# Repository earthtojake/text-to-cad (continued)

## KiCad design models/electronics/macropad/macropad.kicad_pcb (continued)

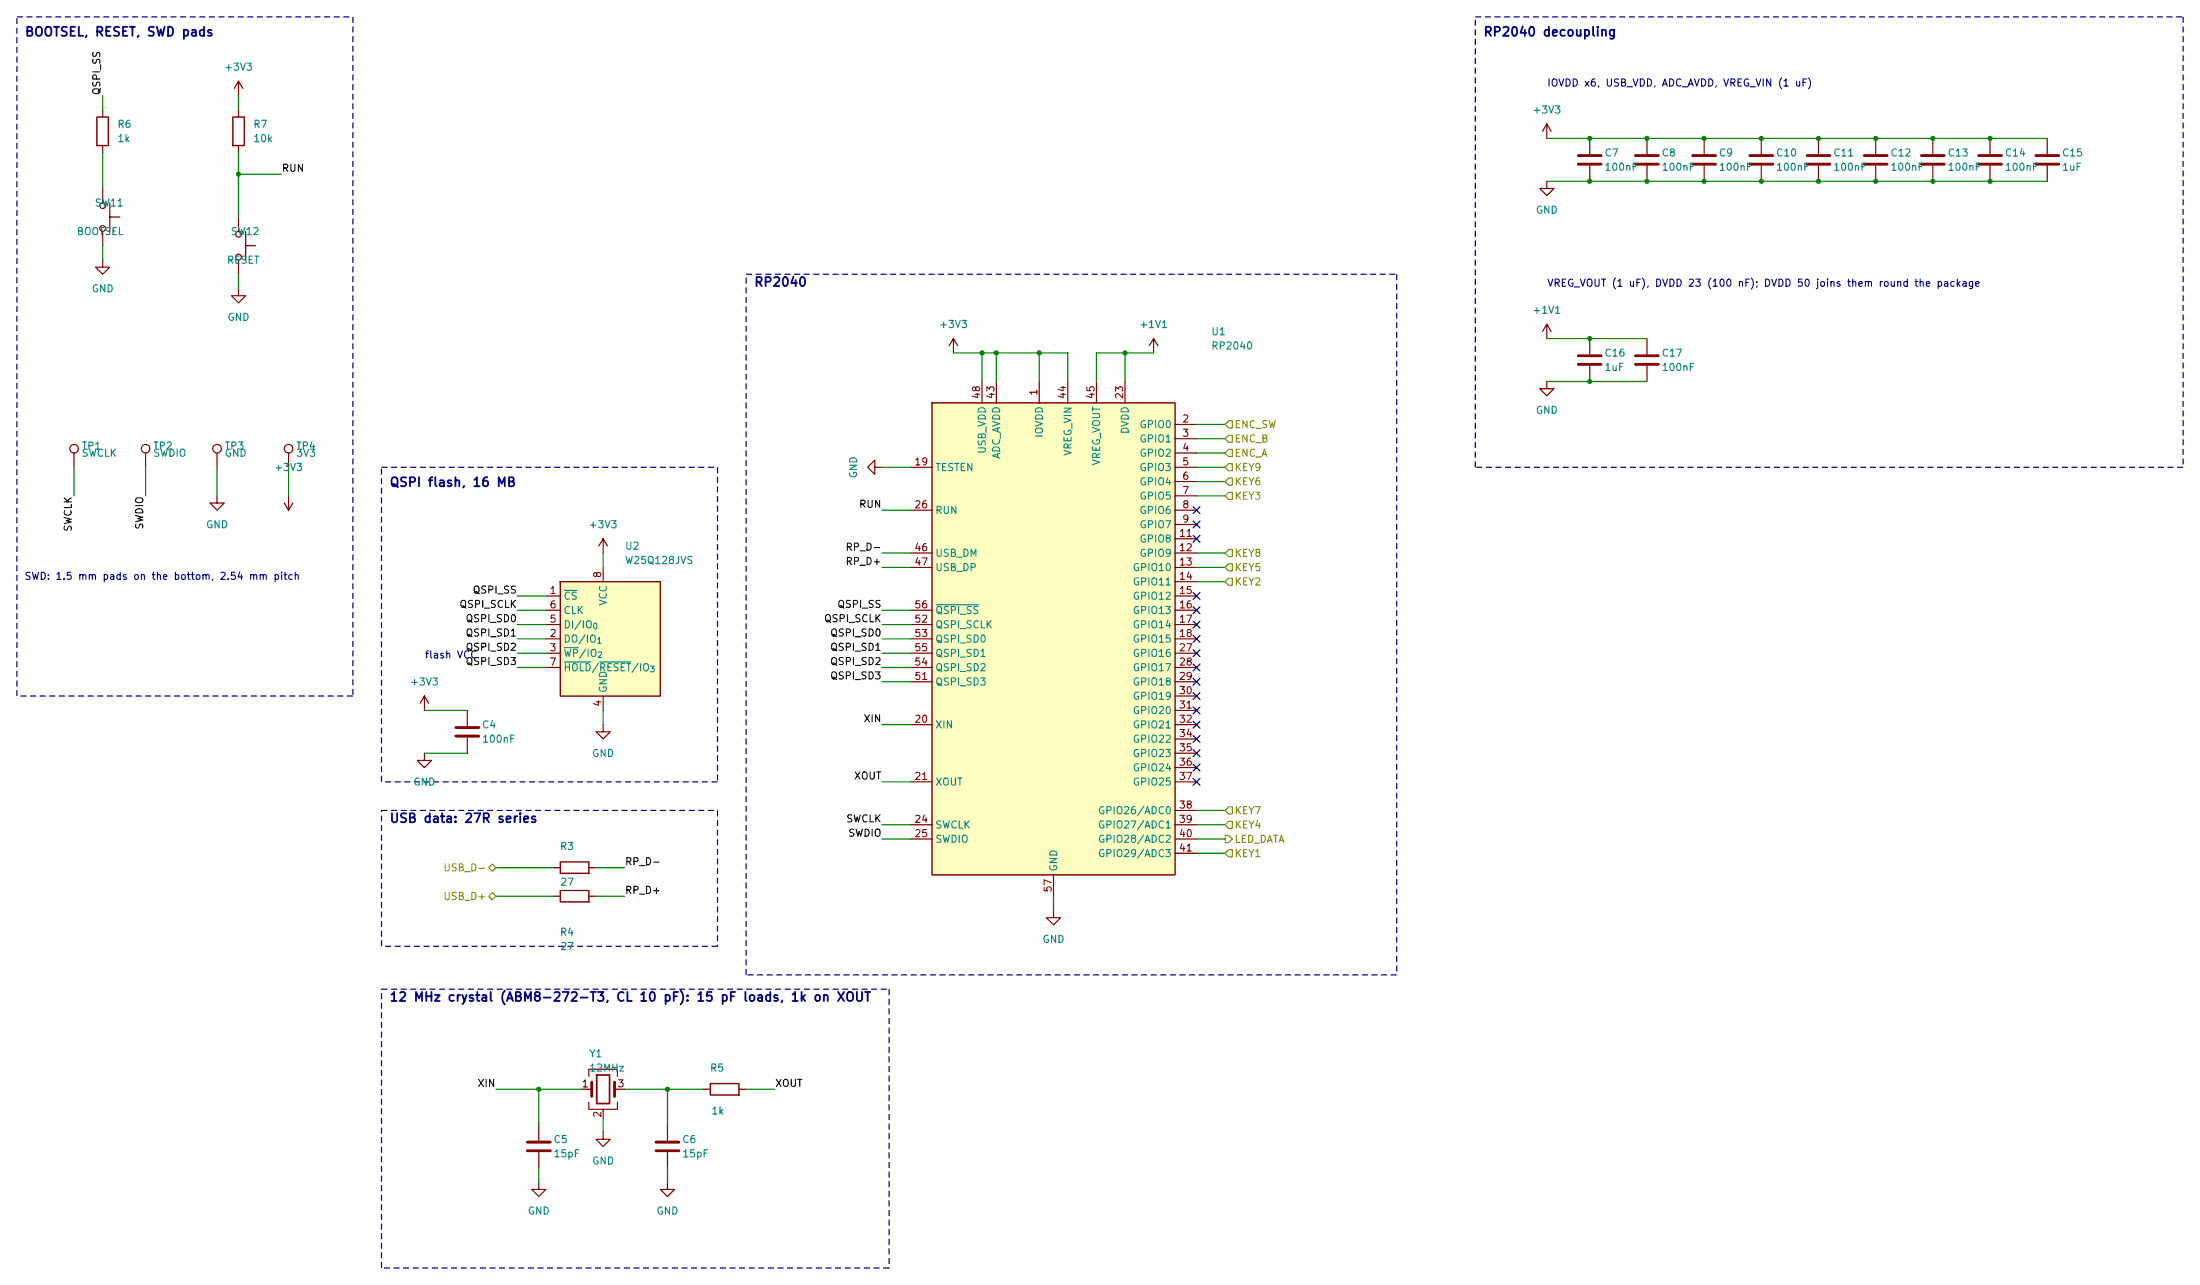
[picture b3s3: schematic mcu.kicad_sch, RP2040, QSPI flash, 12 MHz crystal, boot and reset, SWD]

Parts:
C4, C7, C8, C9, C10, C11, C12, C13, C14, C17: 100nF; C_0402_1005Metric; MPN CL05B104KO5NNNC; LCSC C1525
C5, C6: 15pF; C_0402_1005Metric; MPN CL05C150JB5NNNC; LCSC C1548
C15, C16: 1uF; C_0402_1005Metric; MPN CL05A105KA5NQNC; LCSC C52923
R3, R4: 27; R_0402_1005Metric; MPN 0402WGF270JTCE; LCSC C25100
R5, R6: 1k; R_0402_1005Metric; MPN 0402WGF1001TCE; LCSC C11702
R7: 10k; R_0402_1005Metric; MPN 0402WGF1002TCE; LCSC C25744
SW11: BOOTSEL; SW_SPST_B3U-1000P; MPN B3U-1000P
SW12: RESET; SW_SPST_B3U-1000P; MPN B3U-1000P
TP1: SWCLK; TestPoint_Pad_D1.5mm
TP2: SWDIO; TestPoint_Pad_D1.5mm
TP3: GND; TestPoint_Pad_D1.5mm
TP4: 3V3; TestPoint_Pad_D1.5mm
U1: RP2040; QFN-56-1EP_7x7mm_P0.4mm_EP3.2x3.2mm; MPN RP2040; LCSC C2040
U2: W25Q128JVS; SOIC-8_5.3x5.3mm_P1.27mm; MPN W25Q128JVSIQ; LCSC C97521
Y1: 12MHz; Crystal_SMD_3225-4Pin_3.2x2.5mm; MPN ABM8-272-T3

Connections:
+1V1: C16.1, C17.1, U1.23 (DVDD), U1.45 (VREG_VOUT), U1.50 (DVDD)
+3V3: C4.1, C7.1, C8.1, C9.1, C10.1, C11.1, C12.1, C13.1, C14.1, C15.1, R7.1, TP4.1 (1_1), U1.1 (IOVDD), U1.10 (IOVDD), U1.22 (IOVDD), U1.33 (IOVDD), U1.42 (IOVDD), U1.43 (ADC_AVDD), U1.44 (VREG_VIN), U1.48 (USB_VDD), U1.49 (IOVDD), U2.8 (VCC); also elsewhere on the board
/Keys & LEDs/ENC_A: U1.4 (GPIO2); also elsewhere on the board
/Keys & LEDs/ENC_B: U1.3 (GPIO1); also elsewhere on the board
/Keys & LEDs/ENC_SW: U1.2 (GPIO0); also elsewhere on the board
/Keys & LEDs/KEY1: U1.41 (GPIO29/ADC3); also elsewhere on the board
/Keys & LEDs/KEY2: U1.14 (GPIO11); also elsewhere on the board
/Keys & LEDs/KEY3: U1.7 (GPIO5); also elsewhere on the board
/Keys & LEDs/KEY4: U1.39 (GPIO27/ADC1); also elsewhere on the board
/Keys & LEDs/KEY5: U1.13 (GPIO10); also elsewhere on the board
/Keys & LEDs/KEY6: U1.6 (GPIO4); also elsewhere on the board
/Keys & LEDs/KEY7: U1.38 (GPIO26/ADC0); also elsewhere on the board
/Keys & LEDs/KEY8: U1.12 (GPIO9); also elsewhere on the board
/Keys & LEDs/KEY9: U1.5 (GPIO3); also elsewhere on the board
/Keys & LEDs/LED_DATA: U1.40 (GPIO28/ADC2); also elsewhere on the board
/MCU/QSPI_SCLK: U1.52 (QSPI_SCLK), U2.6 (CLK)
/MCU/QSPI_SD0: U1.53 (QSPI_SD0), U2.5 (DI/IO_{0})
/MCU/QSPI_SD1: U1.55 (QSPI_SD1), U2.2 (DO/IO_{1})
/MCU/QSPI_SD2: U1.54 (QSPI_SD2), U2.3 (~WP/IO_{2})
/MCU/QSPI_SD3: U1.51 (QSPI_SD3), U2.7 (~HOLD/~RESET/IO_{3})
/MCU/QSPI_SS: R6.1, U1.56 (~QSPI_SS), U2.1 (~CS)
/MCU/RP_D+: R4.2, U1.47 (USB_DP)
/MCU/RP_D-: R3.2, U1.46 (USB_DM)
/MCU/RUN: R7.2, SW12.1, U1.26 (RUN)
/MCU/SWCLK: TP1.1 (1_1), U1.24 (SWCLK)
/MCU/SWDIO: TP2.1 (1_1), U1.25 (SWDIO)
/MCU/XIN: C5.1, U1.20 (XIN), Y1.1
/MCU/XOUT: R5.2, U1.21 (XOUT)
/USB & Power/USB_D+: R4.1; also elsewhere on the board
/USB & Power/USB_D-: R3.1; also elsewhere on the board
GND: C4.2, C5.2, C6.2, C7.2, C8.2, C9.2, C10.2, C11.2, C12.2, C13.2, C14.2, C15.2, C16.2, C17.2, SW11.2, SW12.2, TP3.1 (1_1), U1.19 (TESTEN), U1.57 (GND), U2.4 (GND), Y1.2 (G), Y1.4 (G); also elsewhere on the board
unnamed: C6.1, R5.1, Y1.3
unnamed: R6.2, SW11.1

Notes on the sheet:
RP2040
QSPI flash, 16 MB
flash VCC
USB data: 27R series
12 MHz crystal (ABM8-272-T3, CL 10 pF): 15 pF loads, 1k on XOUT
BOOTSEL, RESET, SWD pads
SWD: 1.5 mm pads on the bottom, 2.54 mm pitch
RP2040 decoupling
IOVDD x6, USB_VDD, ADC_AVDD, VREG_VIN (1 uF)
VREG_VOUT (1 uF), DVDD 23 (100 nF); DVDD 50 joins them round the package

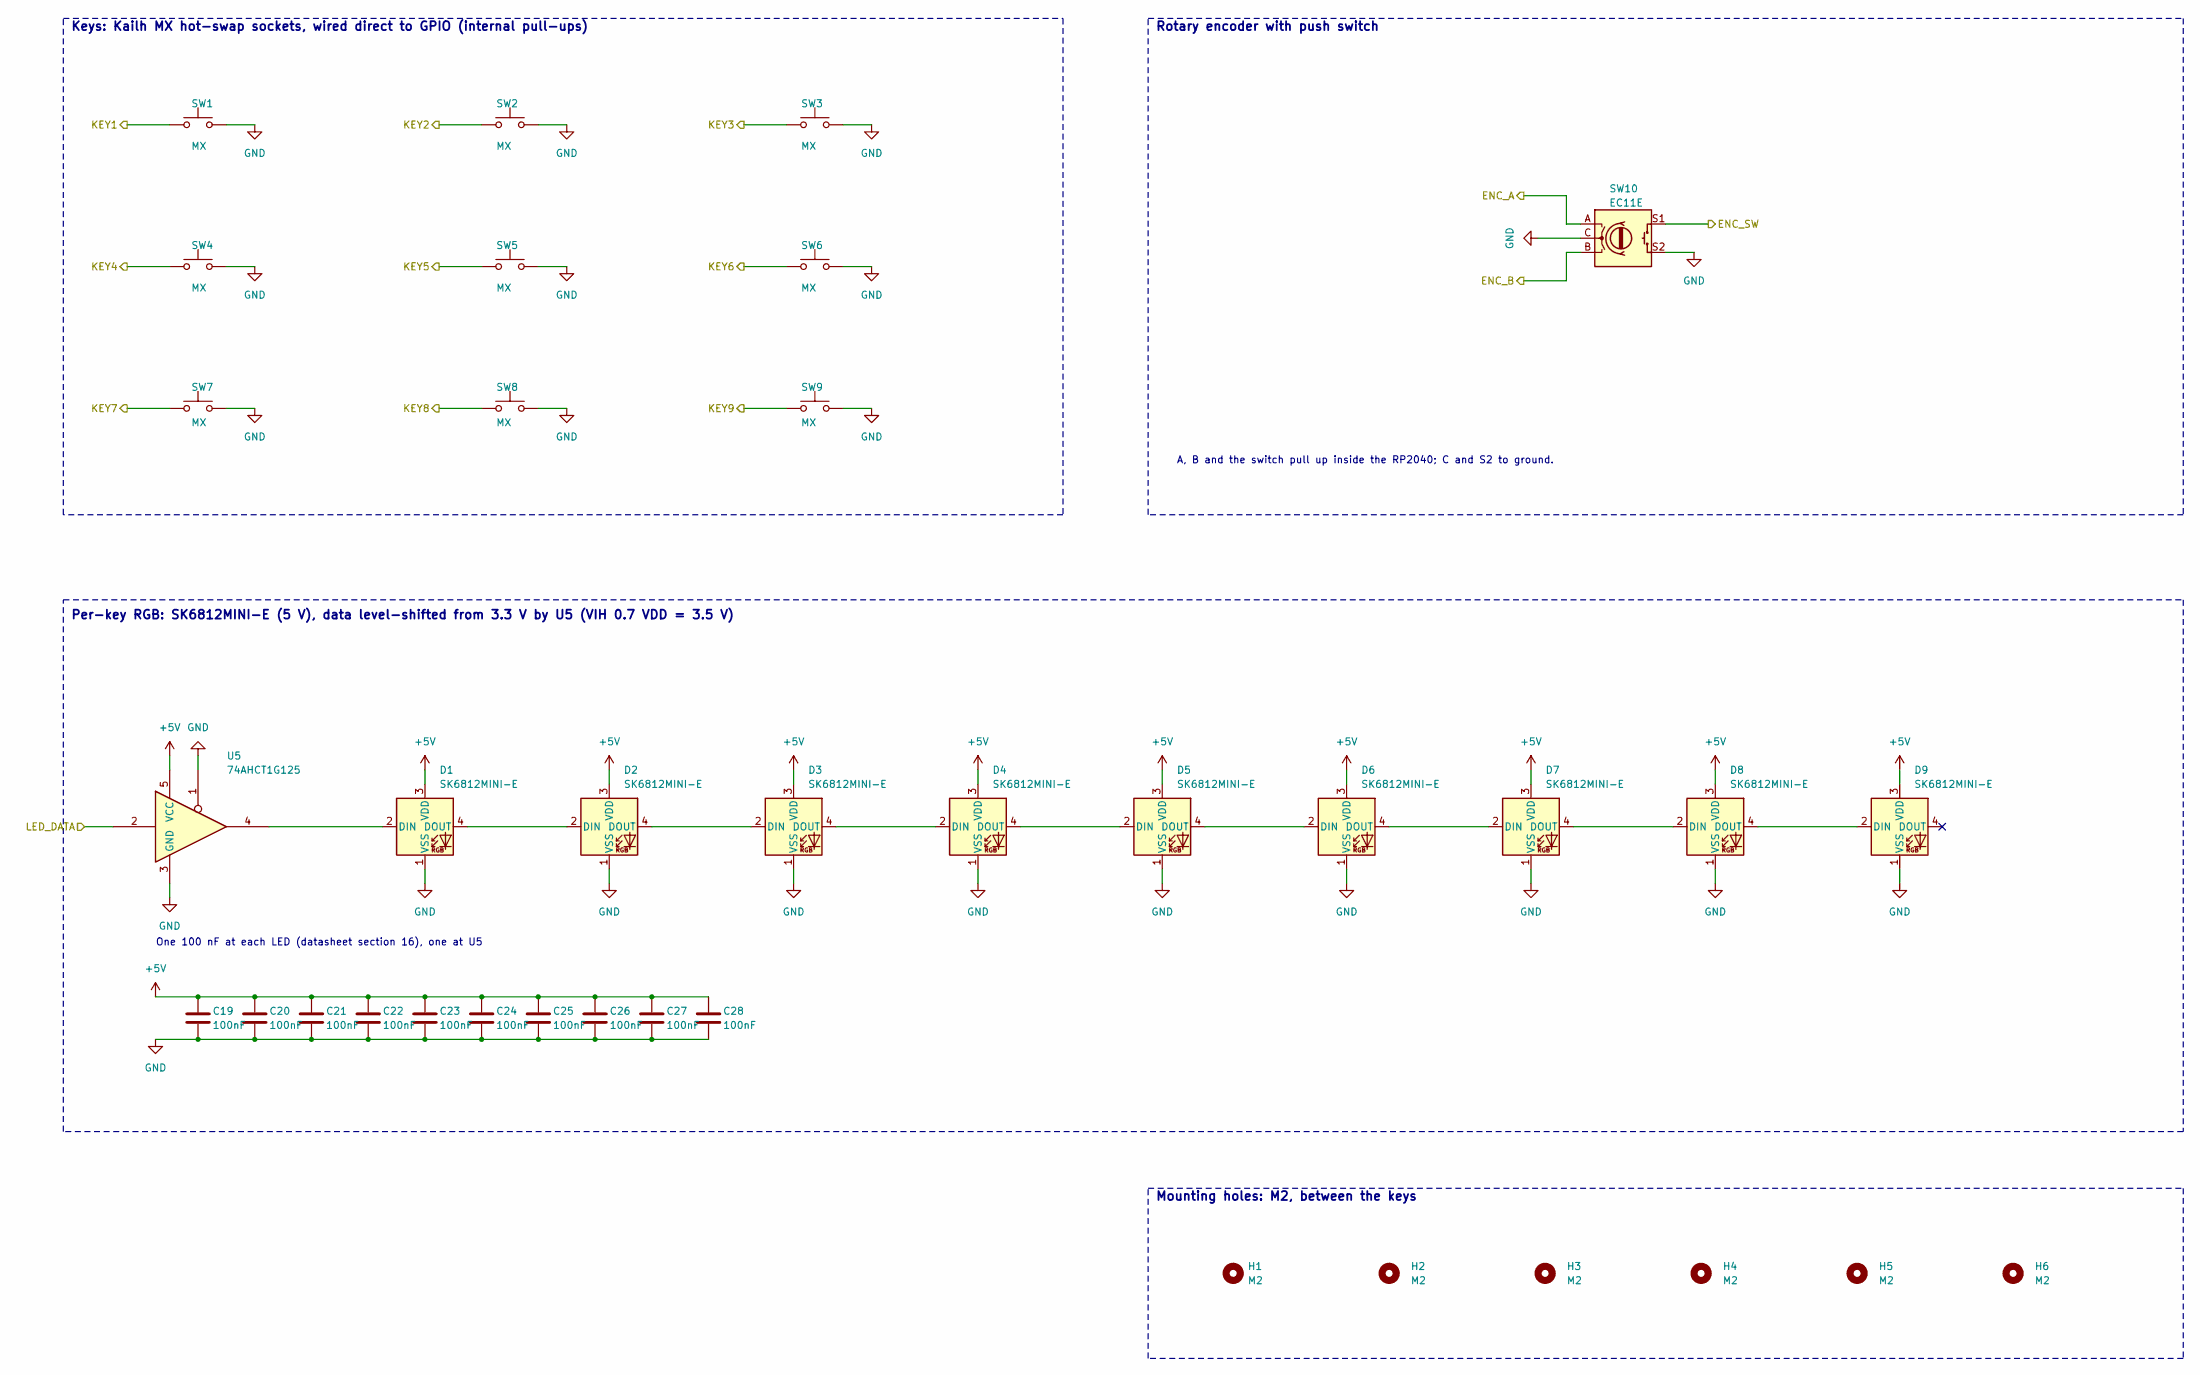
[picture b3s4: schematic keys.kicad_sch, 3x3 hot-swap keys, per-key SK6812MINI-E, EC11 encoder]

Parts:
C19, C20, C21, C22, C23, C24, C25, C26, C27, C28: 100nF; C_0402_1005Metric; MPN CL05B104KO5NNNC; LCSC C1525
D1, D2, D3, D4, D5, D6, D7, D8, D9: SK6812MINI-E; LED_SK6812MINI-E_3.2x2.8mm_P1.5mm_ReverseMount; MPN SK6812MINI-E; LCSC C5149201
H1, H2, H3, H4, H5, H6: M2; MountingHole_2.2mm_M2
SW1, SW2, SW3, SW4, SW5, SW6, SW7, SW8, SW9: MX; SW_Kailh_HotSwap_MX_1.00u; MPN CPG151101S11
SW10: EC11E; RotaryEncoder_Alps_EC11E-Switch_Vertical_H20mm; MPN EC11E18244A5
U5: 74AHCT1G125; SOT-23-5; MPN 74AHCT1G125GV,125

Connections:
+5V: C19.1, C20.1, C21.1, C22.1, C23.1, C24.1, C25.1, C26.1, C27.1, C28.1, D1.3 (VDD), D2.3 (VDD), D3.3 (VDD), D4.3 (VDD), D5.3 (VDD), D6.3 (VDD), D7.3 (VDD), D8.3 (VDD), D9.3 (VDD), U5.5 (VCC); also elsewhere on the board
/Keys & LEDs/ENC_A: SW10.A; also elsewhere on the board
/Keys & LEDs/ENC_B: SW10.B; also elsewhere on the board
/Keys & LEDs/ENC_SW: SW10.S1; also elsewhere on the board
/Keys & LEDs/KEY1: SW1.1; also elsewhere on the board
/Keys & LEDs/KEY2: SW2.1; also elsewhere on the board
/Keys & LEDs/KEY3: SW3.1; also elsewhere on the board
/Keys & LEDs/KEY4: SW4.1; also elsewhere on the board
/Keys & LEDs/KEY5: SW5.1; also elsewhere on the board
/Keys & LEDs/KEY6: SW6.1; also elsewhere on the board
/Keys & LEDs/KEY7: SW7.1; also elsewhere on the board
/Keys & LEDs/KEY8: SW8.1; also elsewhere on the board
/Keys & LEDs/KEY9: SW9.1; also elsewhere on the board
/Keys & LEDs/LED_DATA: U5.2; also elsewhere on the board
GND: C19.2, C20.2, C21.2, C22.2, C23.2, C24.2, C25.2, C26.2, C27.2, C28.2, D1.1 (VSS), D2.1 (VSS), D3.1 (VSS), D4.1 (VSS), D5.1 (VSS), D6.1 (VSS), D7.1 (VSS), D8.1 (VSS), D9.1 (VSS), SW1.2, SW2.2, SW3.2, SW4.2, SW5.2, SW6.2, SW7.2, SW8.2, SW9.2, SW10.C, SW10.S2, U5.1, U5.3 (GND); also elsewhere on the board
unnamed: D1.2 (DIN), U5.4
unnamed: D1.4 (DOUT), D2.2 (DIN)
unnamed: D2.4 (DOUT), D3.2 (DIN)
unnamed: D3.4 (DOUT), D4.2 (DIN)
unnamed: D4.4 (DOUT), D5.2 (DIN)
unnamed: D5.4 (DOUT), D6.2 (DIN)
unnamed: D6.4 (DOUT), D7.2 (DIN)
unnamed: D7.4 (DOUT), D8.2 (DIN)
unnamed: D8.4 (DOUT), D9.2 (DIN)

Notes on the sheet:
Keys: Kailh MX hot-swap sockets, wired direct to GPIO (internal pull-ups)
Rotary encoder with push switch
A, B and the switch pull up inside the RP2040; C and S2 to ground.
Per-key RGB: SK6812MINI-E (5 V), data level-shifted from 3.3 V by U5 (VIH 0.7 VDD = 3.5 V)
One 100 nF at each LED (datasheet section 16), one at U5
Mounting holes: M2, between the keys

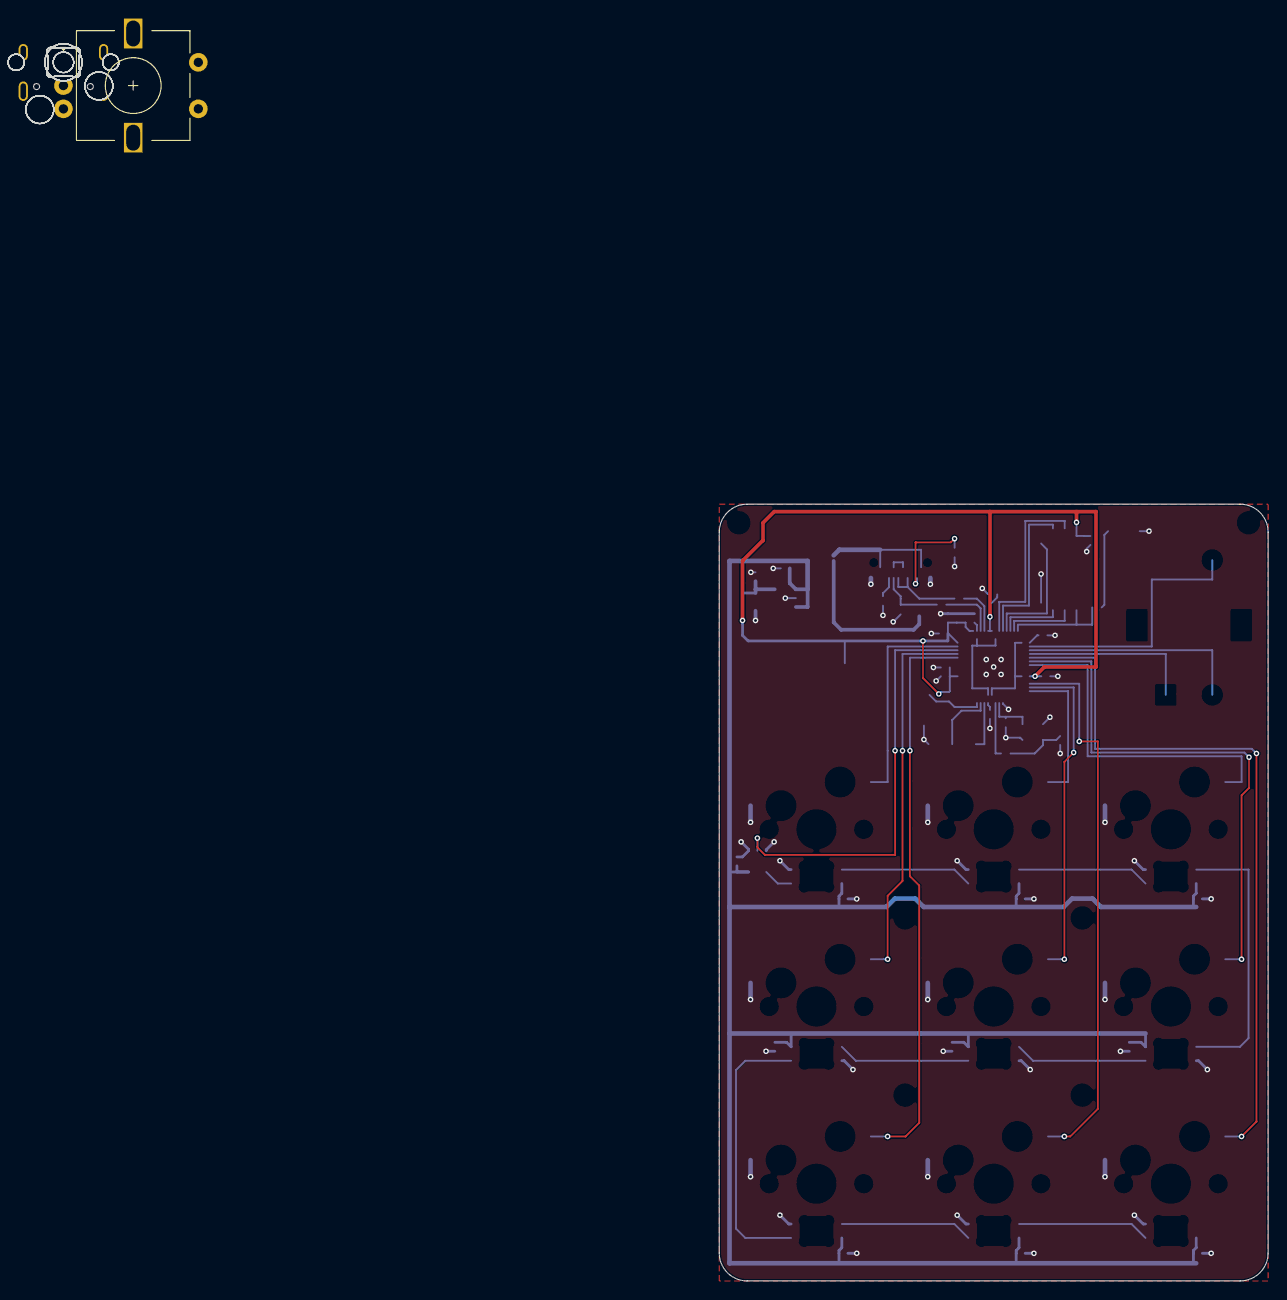
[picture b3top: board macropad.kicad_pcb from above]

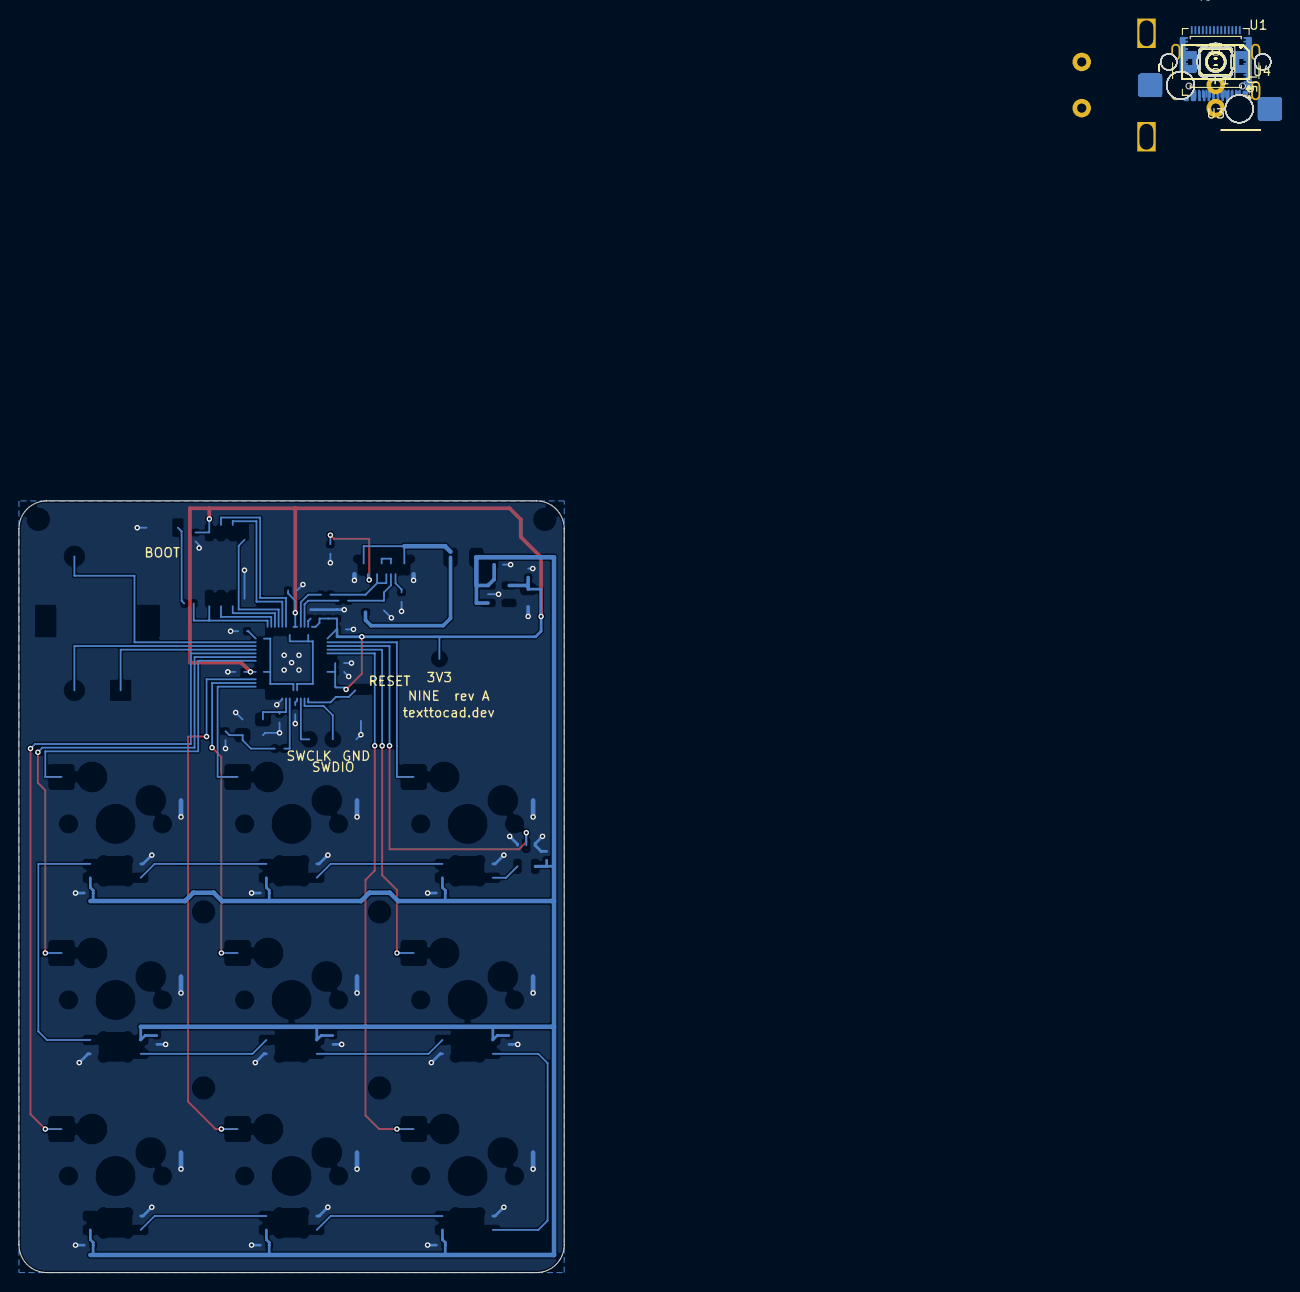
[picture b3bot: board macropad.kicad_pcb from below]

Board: 2 copper layers, 3.6 x 3.2 mm, 73 parts (66 on the bottom side), 46 nets.

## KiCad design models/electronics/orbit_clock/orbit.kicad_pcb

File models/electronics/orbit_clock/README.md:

# Orbit: a round LED ring clock

**Build the board first.** Its KiCad files (the board, the five schematic sheets, the project file, the project
libraries and their tables) are generated by `scripts/`, not committed: `cad run build.py`, from this folder, makes
them in about 30 s. It needs the `cad` command (KiCad 10.99's kicad-cli and API come with it) and KiCad's stock
libraries (macOS's KiCad.app, or `KICAD_STOCK`). Opening the board or the schematic in the viewer or in KiCad,
the checks and the printed parts (`src/`) all read what it writes, so run it before any of them.

A 120 mm round clock face with an outer ring of 60 addressable RGB LEDs (minutes and seconds) and an inner
ring of 12 (hours), an ESP32-C3 on Wi-Fi time, USB-C power and data, auto-dimming from an ambient light
sensor. Three printed parts go round it: a black baffle with a cell for every LED, a thin translucent diffuser,
and a desk stand that holds the clock tilted back 12 degrees with its USB cable hidden underneath.

**Why it is interesting.** The 72 LEDs and 72 capacitors are placed by a few lines of code from a radius and a
count; the LED data chain runs round both rings as copper arcs, one per link; and the baffle's 72 cells line
up with the LEDs because the CAD model reads every LED's position from the saved board file, not from the
script that placed it.

| | |
| --- | --- |
| Board | 120 mm circle with a flat for the USB-C receptacle, 4 layers, 1.6 mm, JLCPCB standard 4-layer rules |
| Parts | 182 footprints: 72 x WS2812B-2020, 72 x 100 nF, ESP32-C3-WROOM-02, USB-C, 26 others |
| Nets | 91; 536 tracks (1.77 m of copper), 71 arcs (the LED chain's links among them), 256 vias |
| Checks | ERC clean (0 warnings); DRC 0 errors, 0 unconnected; 30 warnings: 29 `lib_footprint_mismatch` (footprints placed, turned and flipped over KiCad's API no longer compare equal to their library's) and the module's own silkscreen outline running past the board edge at the antenna |
| Printed | baffle (black PLA), diffuser (natural PETG, 1.2 mm), stand (black PLA); 3MF of each and a two-material front |

## The design

**Front (F.Cu): the face.** The 60 minute LEDs sit on a 50 mm radius, D1 at 12 o'clock, clockwise; the 12 hour
LEDs on a 38 mm radius. Each LED is turned so its local +y points out of the ring: its DOUT (inner row) faces
the next LED and its DIN (outer row) the previous one, so each link is a single arc from one DOUT to the next DIN.
Each LED's 100 nF sits 2.45 mm inside it, with a +5V via and a GND via under its two pads and a GND via outside
the ring at the LED's VSS pad. The ambient light sensor (LTR-303ALS-01, I2C) is at the centre, behind a window
in the baffle. Between the rings at 12 o'clock: the hop from the minute ring's end to the hour ring's start, and
the data input as an arc on a 43.5 mm radius.

**Back (B.Cu): the electronics.** The ESP32-C3-WROOM-02 at the top edge with its antenna at the board's edge and
its own keep-out (no copper on any layer, 5 mm round the antenna, Espressif's rule); the USB-C receptacle on the flat at
the bottom; its USBLC6-2SC6 ESD array in line (flow-through), 5.1k CC pull-downs, a 3 A polyfuse, a 470 uF bulk
capacitor and 22 uF; an AP2112K 3.3 V regulator; a 74AHCT1G125 shifting the LED data from 3.3 V to 5 V with 33 ohm
at the driver; BOOT and RESET; test points for 5V, 3V3, GND, TX and RX (and TP6 at the chain's end on the front).
The CC1/CC2 voltages go to the ESP32's ADC so firmware can cap the LED brightness to what the source advertises.

**Power.** Worst case: 72 LEDs x 3 colours x 12 mA = 2.59 A, plus the ESP32-C3's RF peak (~0.35 A): ~3.0 A, the
most a USB-C source gives at 5 V. The LEDs draw from In2.Cu (a whole-board +5V plane) and return through In1.Cu
(a whole-board GND plane), each by its own vias, so no track carries the ring's current. VBUS runs from both
receptacle pad pairs (0.6 mm stubs, 1.65 A each, IPC-2221 outer 1 oz 10 C), 1.0 mm into the 1210L300 polyfuse
(3 A hold, 6 A trip), out into In2 by two vias. **Why 4 layers:** the 72 LEDs need +5V and GND everywhere round
two rings, the back carries the routing, and the antenna and USB need an unbroken ground: two planes do all three.

**Rules (JLCPCB standard 4-layer, from the pcb skill's manufacturing reference, read 2026-11-04):** 0.15 mm
clearance and minimum track (JLCPCB 0.09/0.09), 0.2 mm signal, 0.6/0.3 mm vias, 0.2 mm minimum drill (the
module's own thermal vias), 0.3 mm copper to edge, 0.19 mm hole clearance (GCT's USB4105 land pattern),
silkscreen 1.0/0.15 mm. Netclasses Default, Power (+5V, VBUS 0.8 mm) and USB in `orbit.kicad_pro`, which `scripts/board.py setup` writes.

**The libraries.** The project carries its own symbols and footprints (`orbit.kicad_sym`, `power.kicad_sym`,
`orbit.pretty`), copied from KiCad's stock ones by `scripts/build_libraries.py`, so ERC and DRC need no library of
the person's. Each footprint names the stock 3D model KiCad's library holds for it (`${KICAD10_3DMODEL_DIR}/...`),
which the board's 3D view and its exports find, but for the two KiCad names and does not ship: the WS2812B-2020
and the LTR-303ALS-01, whose models `src/part_models.py` draws into `orbit.3dshapes/` (`${KIPRJMOD}`).

**The printed parts** (`src/orbit.py`) read the board: the outline (its arc's circle and its flat), the four M3
holes and all 72 LEDs from `orbit.kicad_pcb`, every part's 3D extent from the board's STEP.
- **Baffle**, 8 mm: 60 wedge cells (1.6 mm walls of constant thickness) and 12 round light pipes (7.6 mm), a
  window over the light sensor, pockets underneath for every part outside a cell, M3 pilot holes on the board's
  holes (M3 x 8 self-tapping screws from the back), four peg holes for the diffuser. Prints as modelled, board side
  down.
- **Diffuser**, 1.2 mm natural PETG with a 0.5 mm chamfer and four 3 mm pegs. Prints face down
  (`diffuser_print`). Or print both as one: `front_print` is the diffuser and the baffle stacked as one
  two-material job (face on the plate).
- **Stand**: a 112 x 66 x 34 mm plinth with a saddle that holds the stack by its rim (slot 0.3 mm clear, a lip
  that covers only the outer 4.4 mm of the face, a 6 mm back wall with pockets for the receptacle and the
  polyfuse), tilted back 12 degrees; a pocket for the USB-C plug straight down from the receptacle and a
  45-degree-roofed cable channel under the plinth to the back.

## Files

| Path | What |
| --- | --- |
| `build.py` | the one command that makes the KiCad project: the three scripts below, in order |
| `check_orbit.py` | the board's own checks (schematic vs board, current, decoupling, the antenna keep-out) |
| `scripts/build_libraries.py` | builds the libraries from KiCad's stock ones |
| `scripts/schematic.py` | the schematic |
| `scripts/geometry.py`, `scripts/board.py`, `scripts/routing.py` | the board: setup, place, route, zones, silk |
| `src/part_models.py` | the two 3D models KiCad lacks (WS2812B-2020, LTR-303ALS-01) |
| `src/orbit.py`, `src/check_fit.py`, `src/exports.py` | the printed parts, the assembly and its explode, the fit check, the deliverables |
| `render.py` | the hero still in Blender (below, "Renders") |

Nothing generated is committed: the KiCad project `build.py` writes (`orbit.kicad_pro`, `orbit.kicad_sch` and its
`power`, `mcu`, `minutes` and `hours` sheets, `orbit.kicad_pcb`, all in KiCad 10.99's format, and the libraries
`orbit.kicad_sym`, `power.kicad_sym`, `orbit.pretty/`, `sym-lib-table` and `fp-lib-table`), the two part models
(`orbit.3dshapes/`), the fabrication files (`fab/`), the board's STEP and the printed parts' files (`STEP/`, `XBF/`,
`GLB/`, `3MF/`, `DXF/`) and the renders (`RENDERS/`) are written by the commands below, and `.gitignore` keeps them out of Git.

## Rebuild

From this folder, with the `cad` command:

```bash
# the board and its schematic, from scripts/ (each stage states the board it wants; rerunning is harmless)
cad run build.py                                 # about 30 s: the steps below, in order
#   scripts/build_libraries.py                   the project libraries from KiCad's stock ones
#   scripts/schematic.py                         the schematic (a sheet that holds symbols is left alone)
#   scripts/board.py all                         setup, place, route, zones, silk

# the two 3D models KiCad's library lacks: run this before opening the board in 3D or exporting its STEP or GLB
cad run src/part_models.py                       # orbit.3dshapes/

# check the board
cad kicad_sch erc orbit.kicad_sch
cad kicad_pcb drc orbit.kicad_pcb
cad run check_orbit.py                           # prints nothing when the board is clean

# fabrication files
for k in gerbers drill pos bom pdf; do cad kicad_pcb export orbit.kicad_pcb --to $k -o fab/$k; done
cad kicad_sch export orbit.kicad_sch --to pdf -o fab/schematic
cad kicad_pcb export orbit.kicad_pcb --to dxf -o DXF            # the outline and drilled holes
cad kicad_pcb export orbit.kicad_pcb --to glb -o GLB            # the board with its parts, to look at

# the printed parts, read from the board: its STEP with every part, converted once to an xbf
cad kicad_pcb export orbit.kicad_pcb --to step -o STEP          # STEP/orbit.step
cad step export STEP/orbit.step XBF/orbit.xbf
cad run src/orbit.py                             # prints each model's id
cad run src/check_fit.py                         # interference and clearances, also written to tmp/fit.txt
cad run src/exports.py                           # 3MF/ of each printed part and the two-material front,
                                                 # STEP/orbit_assembly.step, GLB/orbit_assembly.glb
cad threemf dfm 3MF/baffle.3mf --process printing --angle-limit 45 --samples 20000   # and stand.3mf, diffuser.3mf
```

`build_libraries.py` writes the same libraries on every run, and `board.py all` makes the same placement, tracks
and vias. After a board change, export the STEP and the xbf again before
`cad run src/orbit.py`: the printed parts follow.

## Renders

`render.py` is a Blender scene as a plain `import bpy` script, written the render skill's way: the clock at the
end of its explode, out of the stand, with the LEDs lit to show 2:14:23. It reads `GLB/orbit_assembly.glb` (every
part and the explode, `cad run src/exports.py`) and `GLB/orbit.glb` (the board's copper, mask and silkscreen,
`cad kicad_pcb export orbit.kicad_pcb --to glb -o GLB`), laying the board's layers on the assembly's PCB, so make
both first. `cad run` gives it cad's blender integration: Blender's module on Python 3.13, with cad, whose
`cad.blender.load` it loads both GLBs with.

```bash
cad run render.py                                # an EEVEE draft at 1080p, RENDERS/hero-draft.png (15-35 s)
cad run render.py --final                        # Cycles on the GPU, 256 samples, RENDERS/hero.png (about 1.5 min)
cad run render.py --blend                        # either, and the scene as RENDERS/orbit.blend, for Blender 5.2
```

The script is the render's source: nothing in `RENDERS/` is committed. Times are an M1 Max's, the module already
downloaded.

## Checks and their results

- **ERC**: clean, 0 warnings. **Board vs schematic**, pin by pin: 540 pins, 0 differ.
- **DRC** (the board's JLCPCB rules): 0 errors, 0 unconnected; 30 warnings: 29 `lib_footprint_mismatch`
  and the module's own silkscreen outline running past the board edge at the antenna.
- **Antenna**: nothing poured on any layer and no via under the module's keep-out (736 sample points): the rule
  area inside its footprint, which `board.py place` sets from the library footprint after every move, since
  KiPy's move shifts it (it once sat 88 mm right of the module, off the board).
- **Decoupling**: every LED's VDD pad 1.91 mm from its 100 nF; U1 3V3 1.83 mm, U4 2.13 mm, U2 in 2.38 mm, U2 out
  3.13 mm (review: over the 3 mm guide), U5 1.42 mm.
- **Fit** (`src/check_fit.py`, the assembly as built, every board solid against each printed part):
  interference **0.000 mm3** between the board's 598 solids (the PCB and its 172 parts' models) and the
  baffle, the diffuser and the stand, and 0 between the printed parts. Clearances: baffle 0.14 mm over the PCB
  (it rests on it when screwed), 0.40 mm over every part in a pocket (R3/R4/R6/R8/R9, C9/C10, U5); stand
  0.30 mm round the board's rim (the slot), 0.40 mm round the receptacle and the polyfuse; diffuser 0.30 mm from
  the stand; baffle 0.80 mm from the stand.
- **Printing** (`cad threemf dfm --process printing --angle-limit 45 --samples 20000` of each 3MF, the files a
  slicer gets; FDM limits from the cad skill's printing reference): baffle walls p05 1.6 mm (FDM unsupported 1.6:
  pass), 48.6 mm2 of pocket and pilot-hole ceilings (bridges of 2.6-4 mm, under FDM's 10 mm), support 0.2 %; its
  thinnest readings, 0.46 mm, are the webs between the light sensor's window and the pockets of C9 and R9, 0.3 and
  0.4 mm at their thinnest, under FDM's 1.2: review. diffuser walls p05 1.2 mm (supported 1.2: pass), 0.7 mm at the
  rim its 0.5 mm chamfer thins, the chamfer within a hair of 45 degrees (132 mm2 under it in the 3MF's mesh), on
  the first layer. stand walls p05 6.0 mm (pass), 245 mm2 at exactly 45 degrees (the cable channel's roofs and the
  plug pocket's lip), support 1.4 %; its thinnest is a 0.9 mm skin at the cradle's back behind the USB plug's
  pocket, under FDM's 1.2: review. Fixed on the way: the stand's arc-sided saddle (1,356 mm2 overhanging, now
  straight-sided), flat channel ceilings (now 45-degree roofs), the diffuser printed face down, and peg holes
  0.87 mm from the minute cells (moved in to 42 mm). Not measured by the check: minimum hole (the 2.6 mm pilots
  are over FDM's 2.0), minimum feature, bridge length.

## Assembly

1. Print the stand and the baffle in black PLA, the diffuser in natural PETG (or `front_two_material.3mf` on a
   two-filament printer).
2. Press the diffuser's pegs into the baffle, set the baffle on the board's face (the cells over the LEDs; the
   flat at the bottom) and fix it with four M3 x 8 self-tapping screws from the back.
3. Drop the stack into the stand's slot, the flat down, then plug the USB-C cable up through the plinth.

## Demo video script

The pitch: *"72 LEDs placed by a few lines of code, a data chain routed as arcs round two rings, and 72 printed
cells that line up because the CAD reads the same board."*

| # | The prompt (typed to the agent) | What the viewer shows | Time | Why it lands |
| --- | --- | --- | --- | --- |
| 1 | "Design a round 120 mm LED ring clock: 60 minute LEDs, 12 hour LEDs, an ESP32-C3, USB-C power. Start with the schematic." | The schematic: root sheet with four sheet symbols, then the Minute ring sheet (60 LEDs chained) | 25 s | A hierarchical schematic, ERC clean, from one sentence |
| 2 | "Place the LEDs on the board from a radius and a count, each with its capacitor beside it." | The board in 2D, `placement` view: 72 LEDs and 72 caps snapping into two perfect rings, ratsnest lines | 25 s | Parametric placement: change `R_MINUTE` and the ring moves |
| 3 | "Route the LED data chain round the rings as arcs." | Copper view, zoom on the ring: the smooth arcs, DOUT to DIN, the hop between the rings at 12 | 30 s | Arcs, not jagged segments, all from code |
| 4 | "Show me the back." | Flip, to the bottom: the ESP32 at the top edge with its antenna keep-out, USB-C on the flat, the regulator, level shifter | 20 s | Two-sided, 4 layers, a real power design (3 A worst case in the planes) |
| 5 | "Show it in 3D." | The corner's 2D/3D button: the board with every part's 3D model, orbiting round the LED rings | 30 s | THE shot: 144 tiny parts in two rings, in 3D, in the browser |
| 6 | "Now design a baffle with a cell for every LED, read from the board, and a diffuser and a stand." | The baffle: 60 wedge cells and 12 light pipes; the stand with its slot | 25 s | The cells come from the board file, not a copy of its numbers |
| 7 | "Prove it fits." | Terminal: interference 0 mm3 between the board's 172 parts and the baffle, diffuser and stand | 15 s | A measured fit, not a picture |
| 8 | "Play the explode." | The assembly: the diffuser flies forward, then the baffle, then the board rises out of the stand | 25 s | The 72 cells over the 72 LEDs, visible as the parts separate |
| 9 | "Export it for JLCPCB and my printer." | fab/ (Gerbers, BOM, placement) and 3MF/, including a two-material front | 15 s | From a sentence to fab files and prints |

Shots 5 and 8 are the centre of the video: give them the most time, orbit slowly in 5, and play 8 twice. Run
`cad run src/part_models.py` before shot 5, or the 72 LEDs and the sensor stand as blocks; the fit check takes
several minutes, so run it before the take and show its output.

## Sources

- WS2812B-2020 (Worldsemi, datasheet V1.3 as KiCad cites it): 2.0 x 2.0 mm, 12 mA a channel.
- WS2812B-Mini pinout (Worldsemi datasheets, e.g. https://learn.watterott.com/kb/ws281x/WS2812B-Mini-v3.pdf).
- Littelfuse 1210L300SLWR: 3 A hold, 6 A trip, 6 V (https://www.lcsc.com/product-detail/C3762168.html).
- ESP32-C3-WROOM-02 datasheet (Espressif, the footprint's link): antenna keep-out, strapping pins IO2/IO8/IO9.
- JLCPCB capabilities as tabulated in the pcb skill (manufacturing.md, read 2026-11-04).

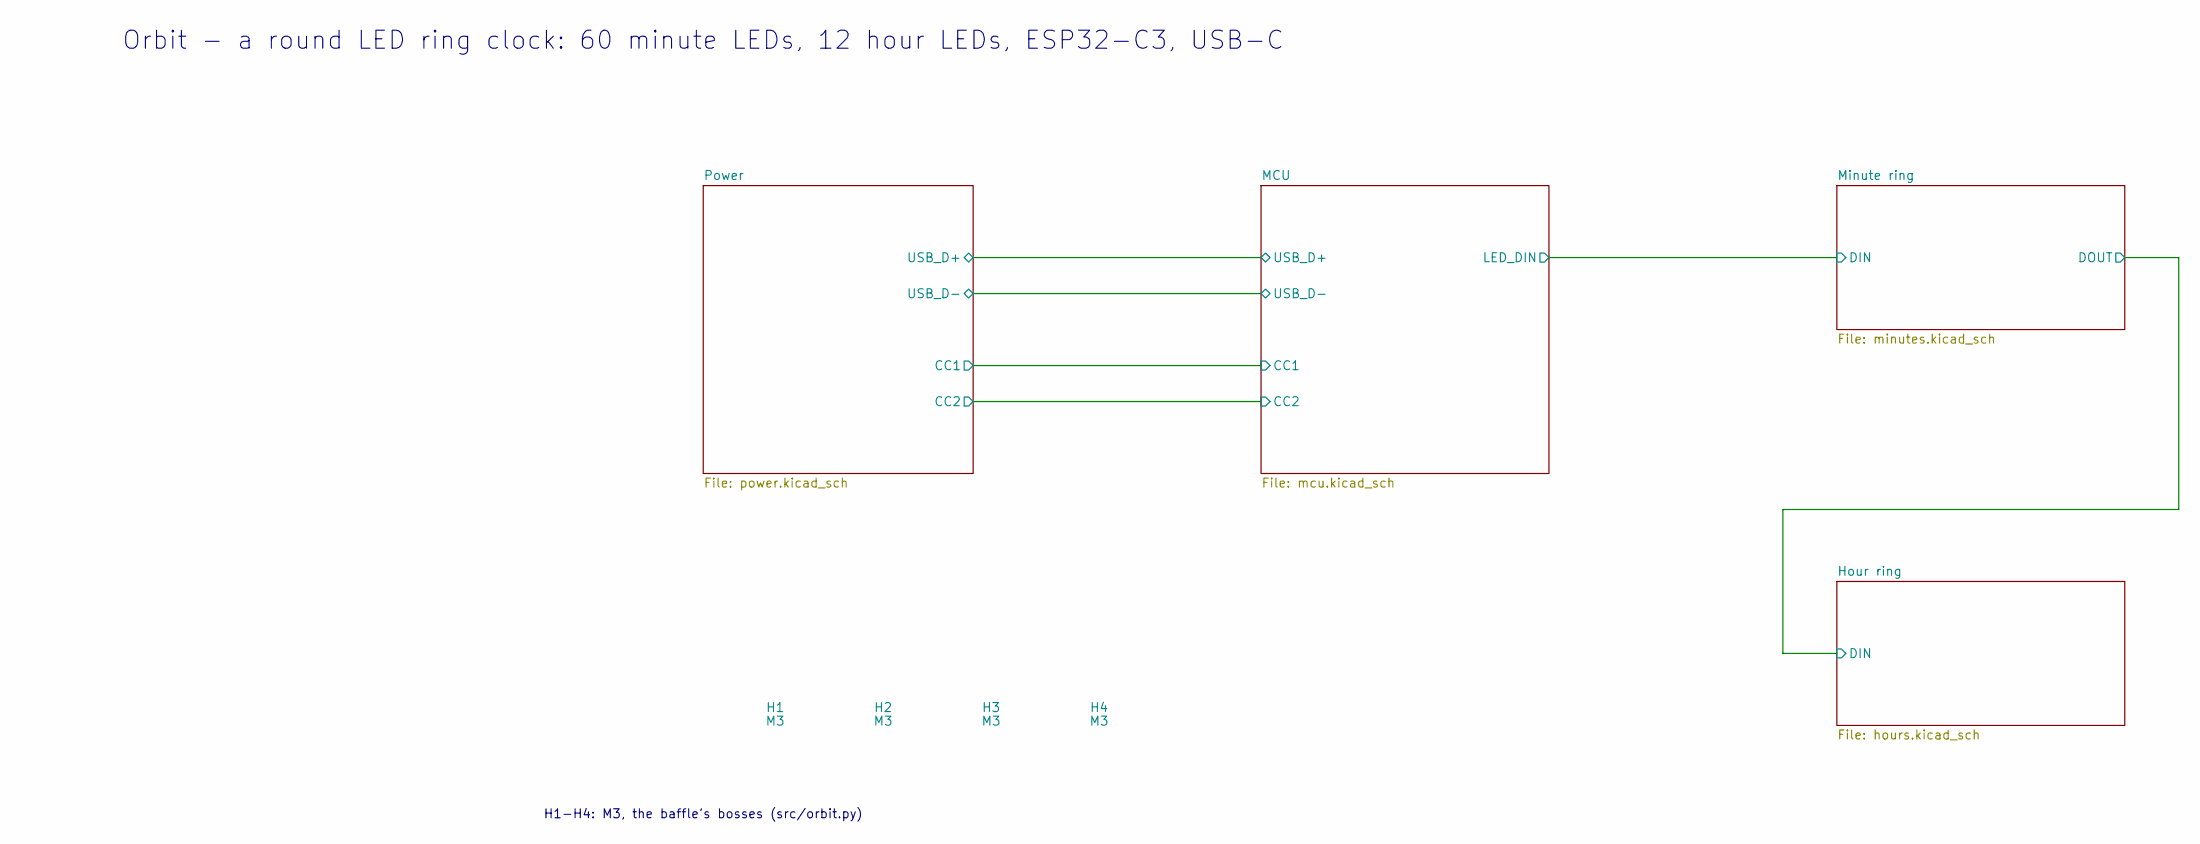
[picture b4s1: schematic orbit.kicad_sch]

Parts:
H1, H2, H3, H4: M3; MountingHole_3.2mm_M3

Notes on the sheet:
Orbit - a round LED ring clock: 60 minute LEDs, 12 hour LEDs, ESP32-C3, USB-C
H1-H4: M3, the baffle's bosses (src/orbit.py)

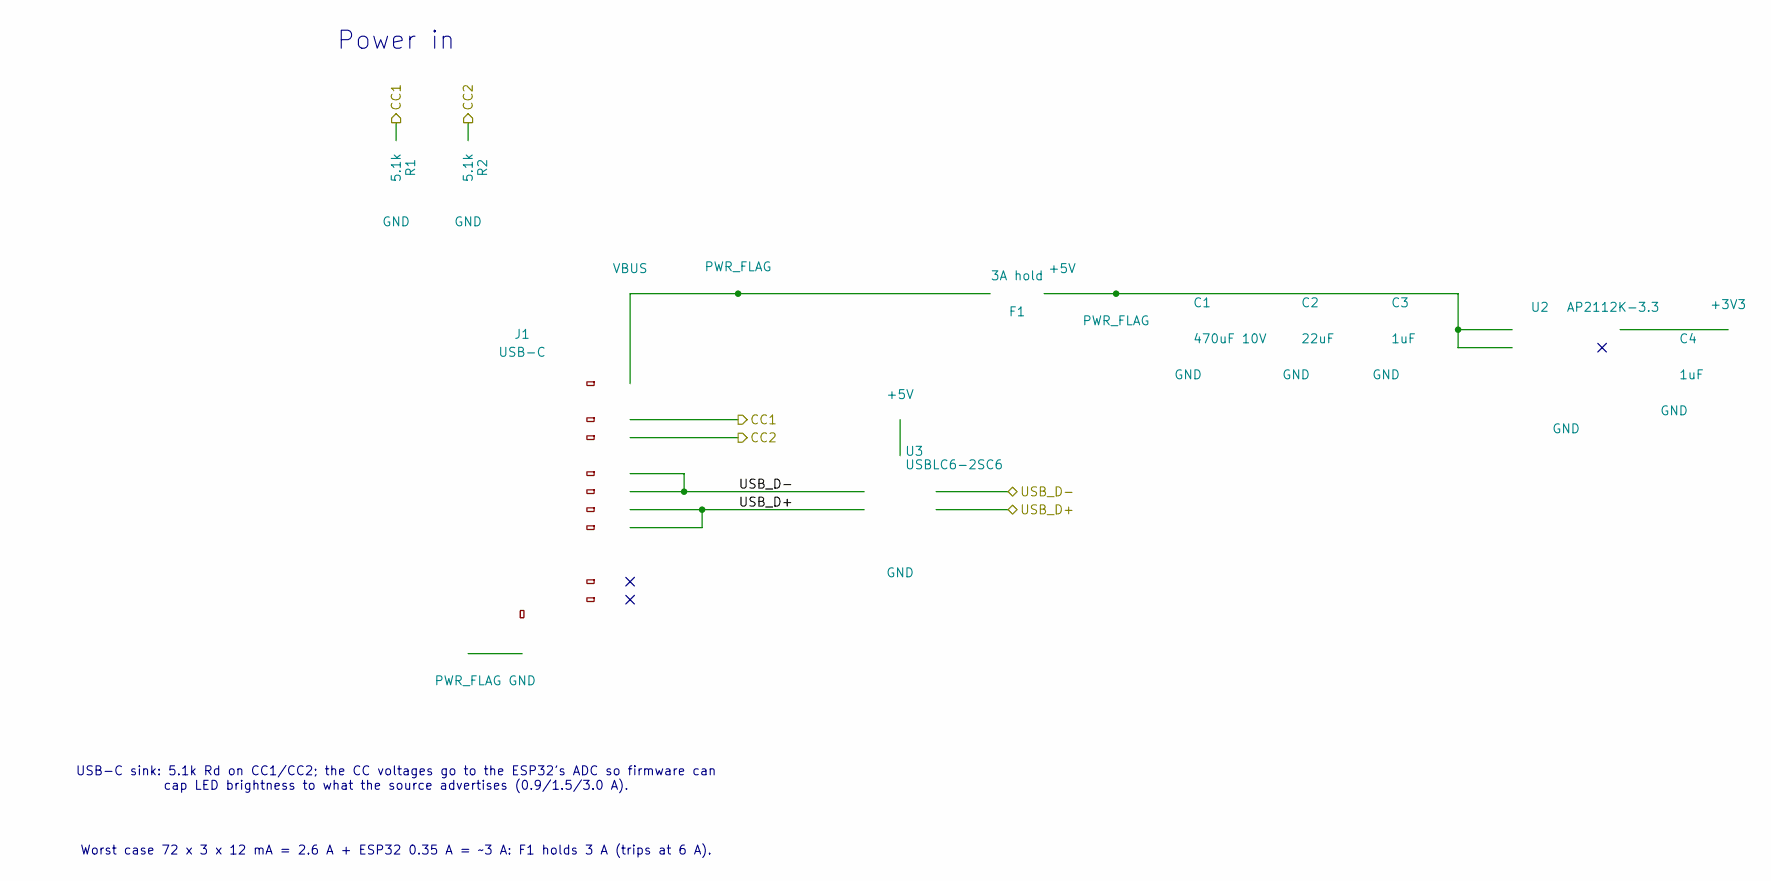
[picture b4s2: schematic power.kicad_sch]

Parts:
C1: 470uF 10V; CP_Elec_8x10; MPN EEE-FK1A471P
C2: 22uF; C_1206_3216Metric; MPN CL31A226KAHNNNE
C3, C4: 1uF; C_0603_1608Metric; MPN CL10A105KB8NNNC
F1: 3A hold; Fuse_1210_3225Metric; MPN 1210L300SLWR
J1: USB-C; USB_C_Receptacle_GCT_USB4105-xx-A_16P_TopMnt_Horizontal; MPN USB4105-GF-A
R1, R2: 5.1k; R_0603_1608Metric; MPN RC0603FR-075K1L
U2: AP2112K-3.3; SOT-23-5; MPN AP2112K-3.3TRG1
U3: USBLC6-2SC6; SOT-23-6; MPN USBLC6-2SC6

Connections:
+3V3: C4.1, U2.5 (VOUT); also elsewhere on the board
+5V: C1.1, C2.1, C3.1, F1.2, U2.1 (VIN), U2.3 (EN), U3.5 (VBUS); also elsewhere on the board
/MCU/CC1: J1.A5 (CC1), R1.1; also elsewhere on the board
/MCU/CC2: J1.B5 (CC2), R2.1; also elsewhere on the board
/Power/USB_D+: J1.A6 (D+), J1.B6 (D+), U3.3 (I/O2), U3.4 (I/O2); also elsewhere on the board
/Power/USB_D-: J1.A7 (D-), J1.B7 (D-), U3.1 (I/O1), U3.6 (I/O1); also elsewhere on the board
GND: C1.2, C2.2, C3.2, C4.2, J1.A1 (GND), J1.A12 (GND), J1.B1 (GND), J1.B12 (GND), J1.SH (SHIELD), R1.2, R2.2, U2.2 (GND), U3.2 (GND); also elsewhere on the board
VBUS: F1.1, J1.A4 (VBUS), J1.A9 (VBUS), J1.B4 (VBUS), J1.B9 (VBUS)

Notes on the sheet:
Worst case 72 x 3 x 12 mA = 2.6 A + ESP32 0.35 A = ~3 A: F1 holds 3 A (trips at 6 A).
USB-C sink: 5.1k Rd on CC1/CC2; the CC voltages go to the ESP32's ADC so firmware can cap LED brightness to what the source advertises (0.9/1.5/3.0 A).
Power in
